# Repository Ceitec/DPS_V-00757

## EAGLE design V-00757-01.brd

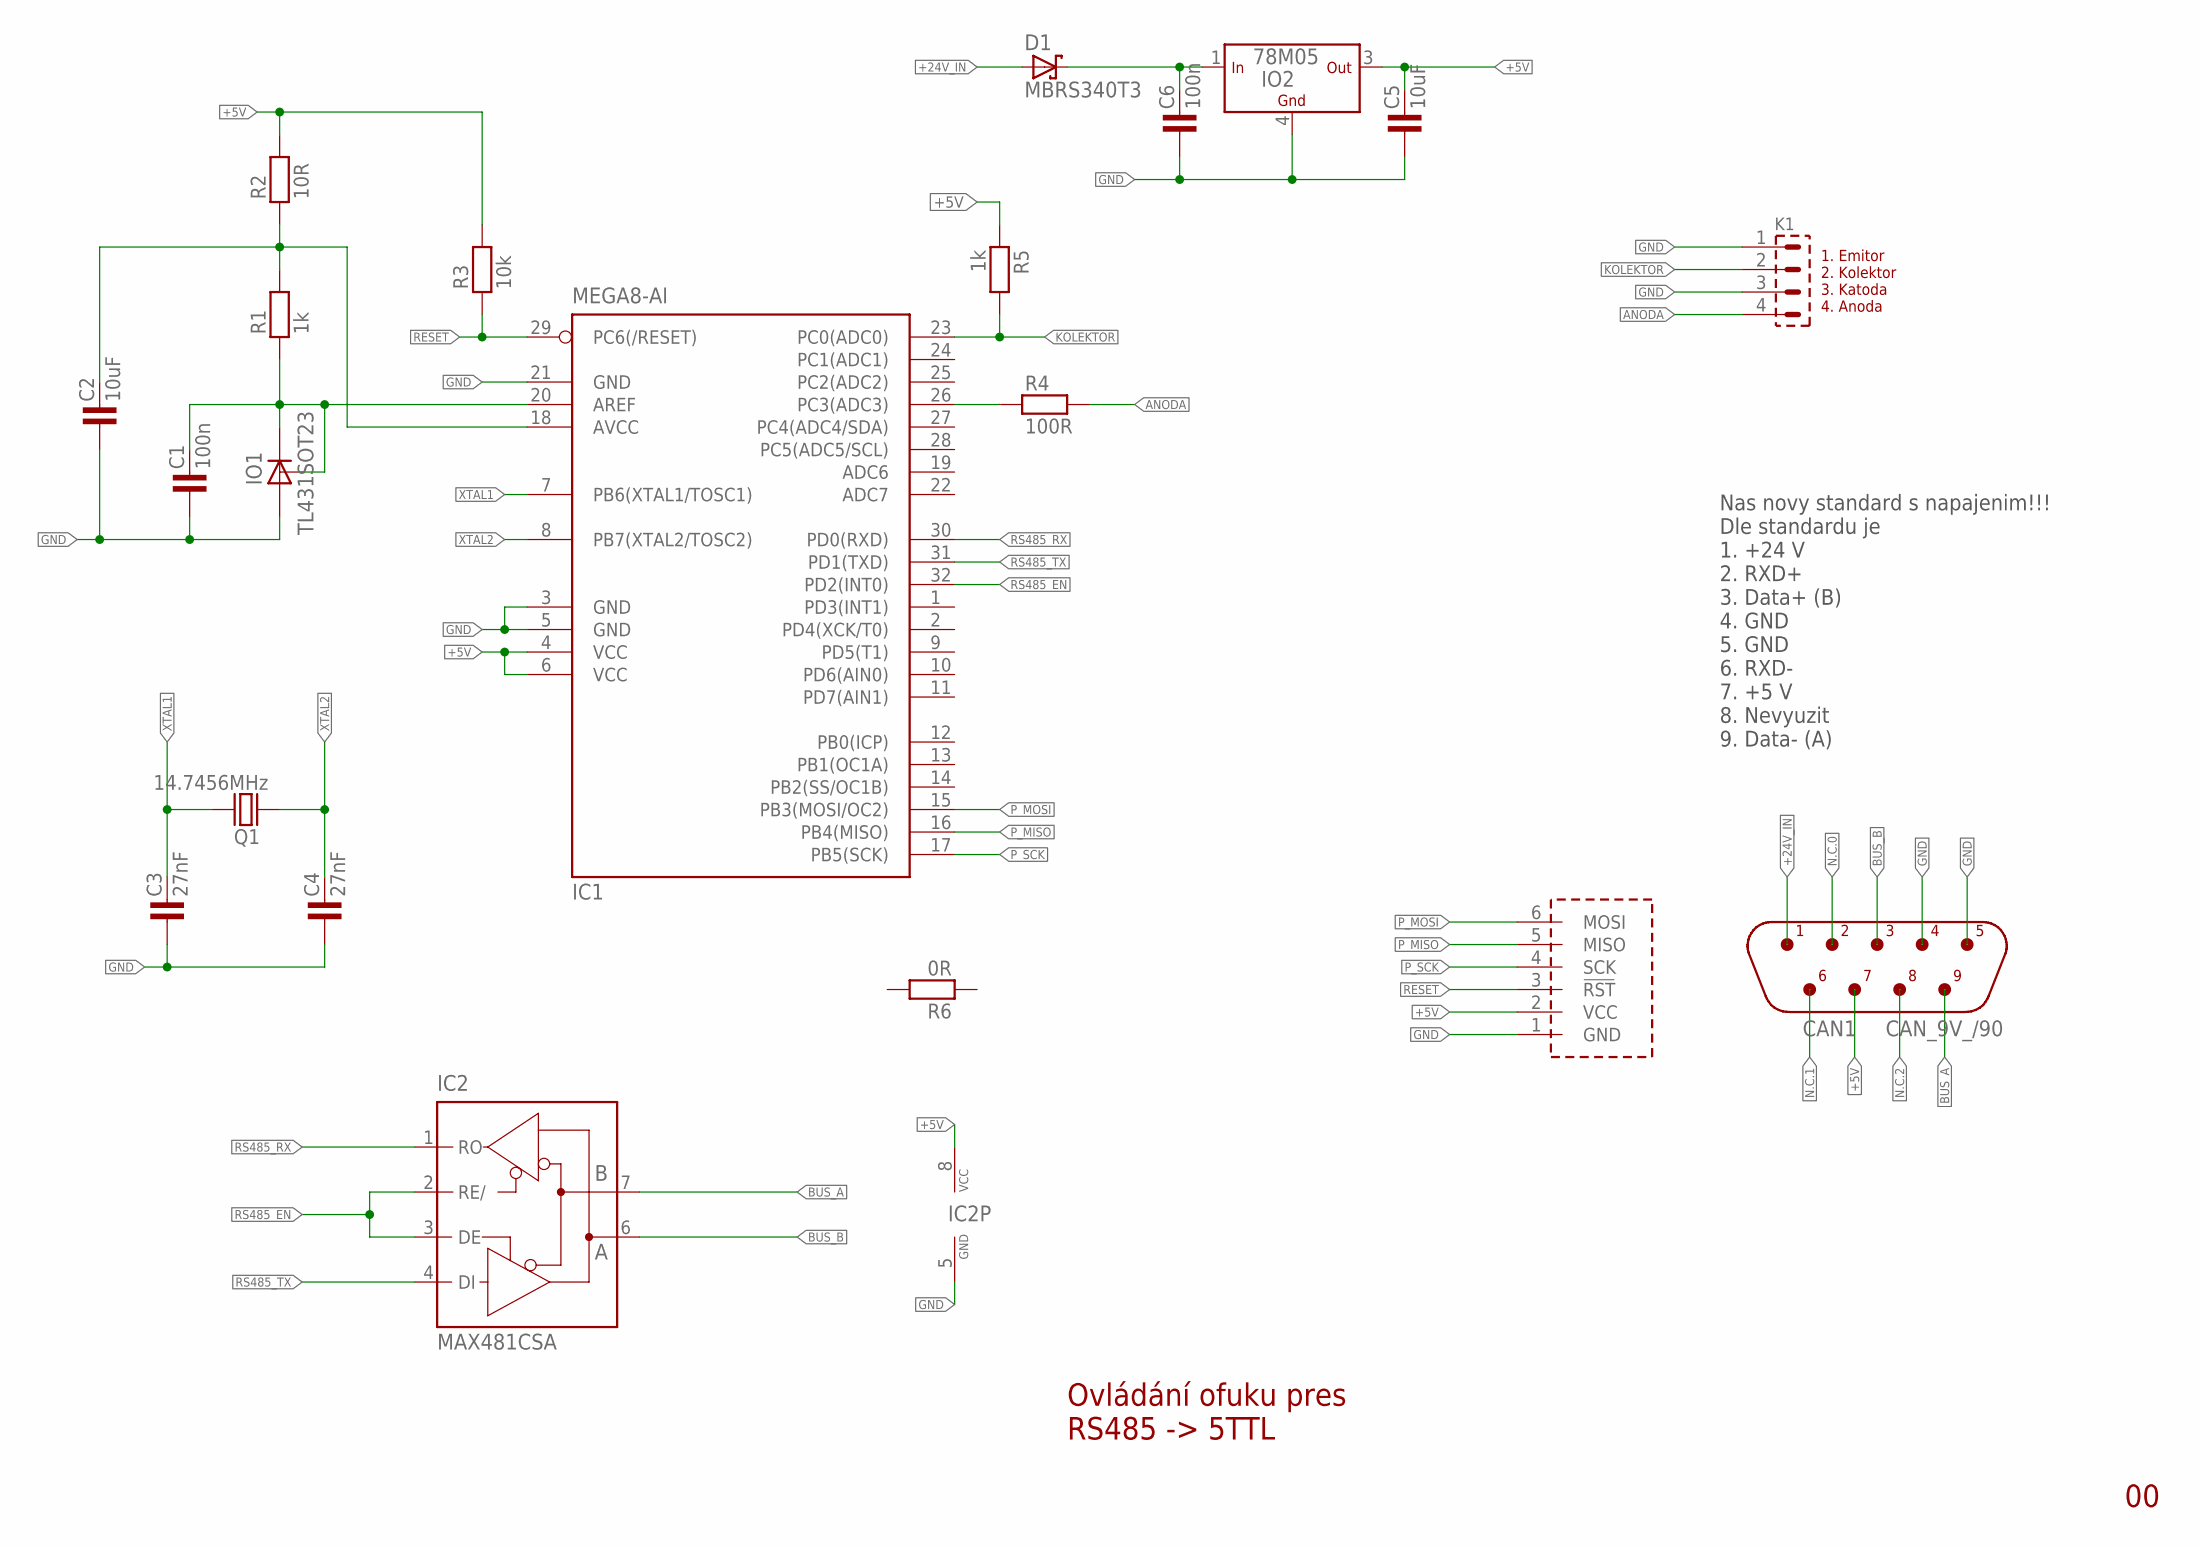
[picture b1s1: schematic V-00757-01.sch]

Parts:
C1, C6: 100n; 1206
C2, C5: 10uF; 1206
C3, C4: 27nF; 0805
CAN1: CAN_9V_/90; CAN9V/90
D1: MBRS340T3; SMC
IC1: MEGA8-AI; TQFP32-08
IC2: MAX481CSA; SO08
IO1: TL431SOT23; SOT23
IO2: 78M05; DPAK
K1: PSH02-04W
Q1: 14.7456MHz; HC-49U
R1, R5: 1k; 1206
R2: 10R; 1206
R3: 10k; 1206
R4: 100R; 1206
R6: 0R; 1206
U$1: AVR_PROG_SPI; PSH02-06P

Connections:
+5V: C5.2, CAN1.7, IC1.4 (VCC), IC1.6 (VCC), IC2.8 (VCC), IO2.3 (OUT), R2.2, R3.2, R5.1, U$1.2 (VCC)
+24V: C6.2, D1.C, IO2.1 (IN)
+24V_IN: CAN1.1, D1.A
ANODA: K1.4, R4.2
BUS_A: CAN1.9, IC2.7 (B)
BUS_B: CAN1.3, IC2.6 (A)
GND: C1.1, C2.1, C3.1, C4.1, C5.1, C6.1, CAN1.4, CAN1.5, IC1.3 (GND), IC1.5 (GND), IC1.21 (GND), IC2.5 (GND), IO1.3 (A), IO2.4 (GND), K1.1, K1.3, U$1.1 (GND)
KOLEKTOR: IC1.23 (PC0(ADC0)), K1.2, R5.2
unnamed: C1.2, IC1.20 (AREF), IO1.1 (C), IO1.2 (R), R1.1
unnamed: IC1.26 (PC3(ADC3)), R4.1
unnamed: C2.2, IC1.18 (AVCC), R1.2, R2.1
N.C.0: CAN1.2
N.C.1: CAN1.6
N.C.2: CAN1.8
P_MISO: IC1.16 (PB4(MISO)), U$1.5 (MISO)
P_MOSI: IC1.15 (PB3(MOSI/OC2)), U$1.6 (MOSI)
P_SCK: IC1.17 (PB5(SCK)), U$1.4 (SCK)
RESET: IC1.29 (PC6(/RESET)), R3.1, U$1.3 (!RST)
RS485_EN: IC1.32 (PD2(INT0)), IC2.2 (RE/), IC2.3 (DE)
RS485_RX: IC1.30 (PD0(RXD)), IC2.1 (RO)
RS485_TX: IC1.31 (PD1(TXD)), IC2.4 (DI)
XTAL1: C3.2, IC1.7 (PB6(XTAL1/TOSC1)), Q1.2
XTAL2: C4.2, IC1.8 (PB7(XTAL2/TOSC2)), Q1.1

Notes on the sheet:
Ovládání ofuku pres RS485 -> 5TTL
1. Emitor 2. Kolektor 3. Katoda 4. Anoda
Nas novy standard s napajenim!!! Dle standardu je 1. +24 V 2. RXD+ 3. Data+ (B) 4. GND 5. GND 6. RXD- 7. +5 V 8. Nevyuzit 9. Data- (A)

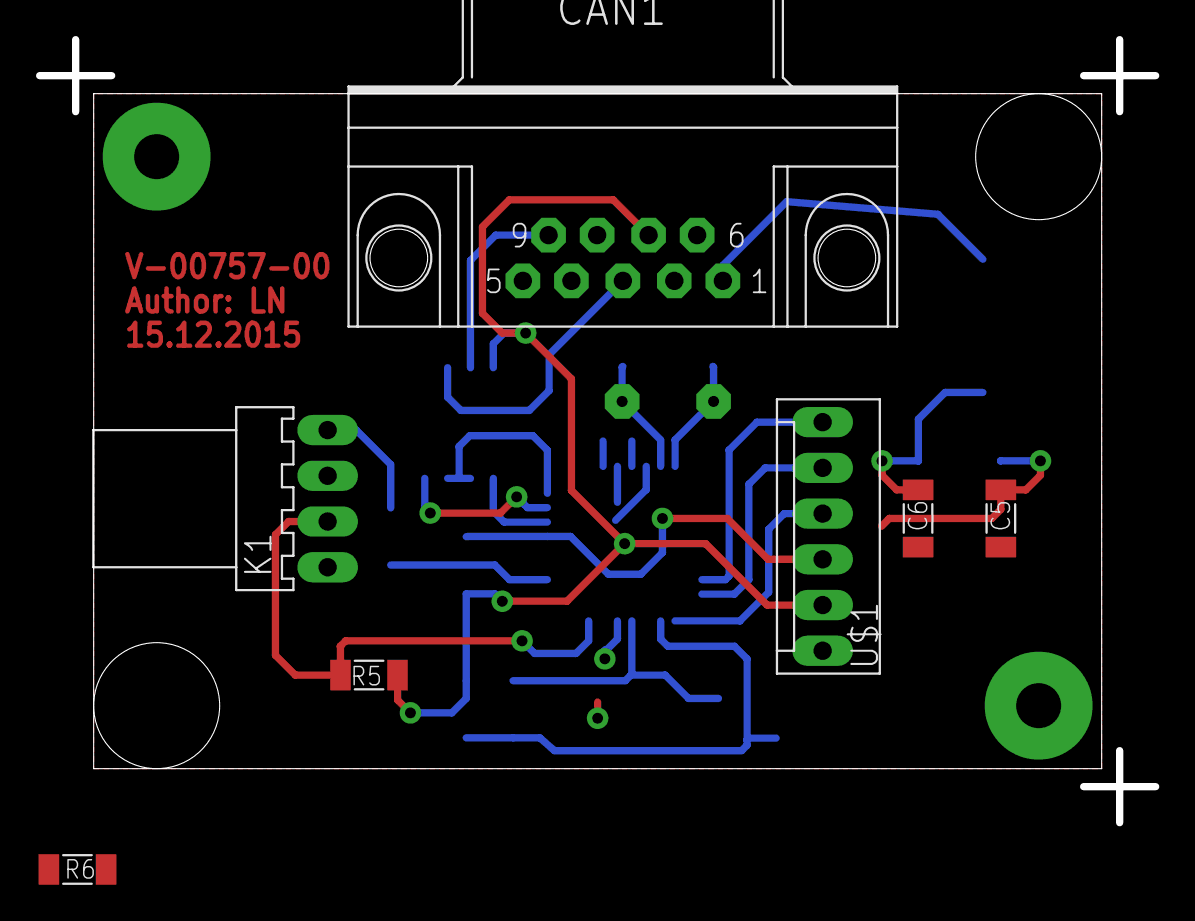
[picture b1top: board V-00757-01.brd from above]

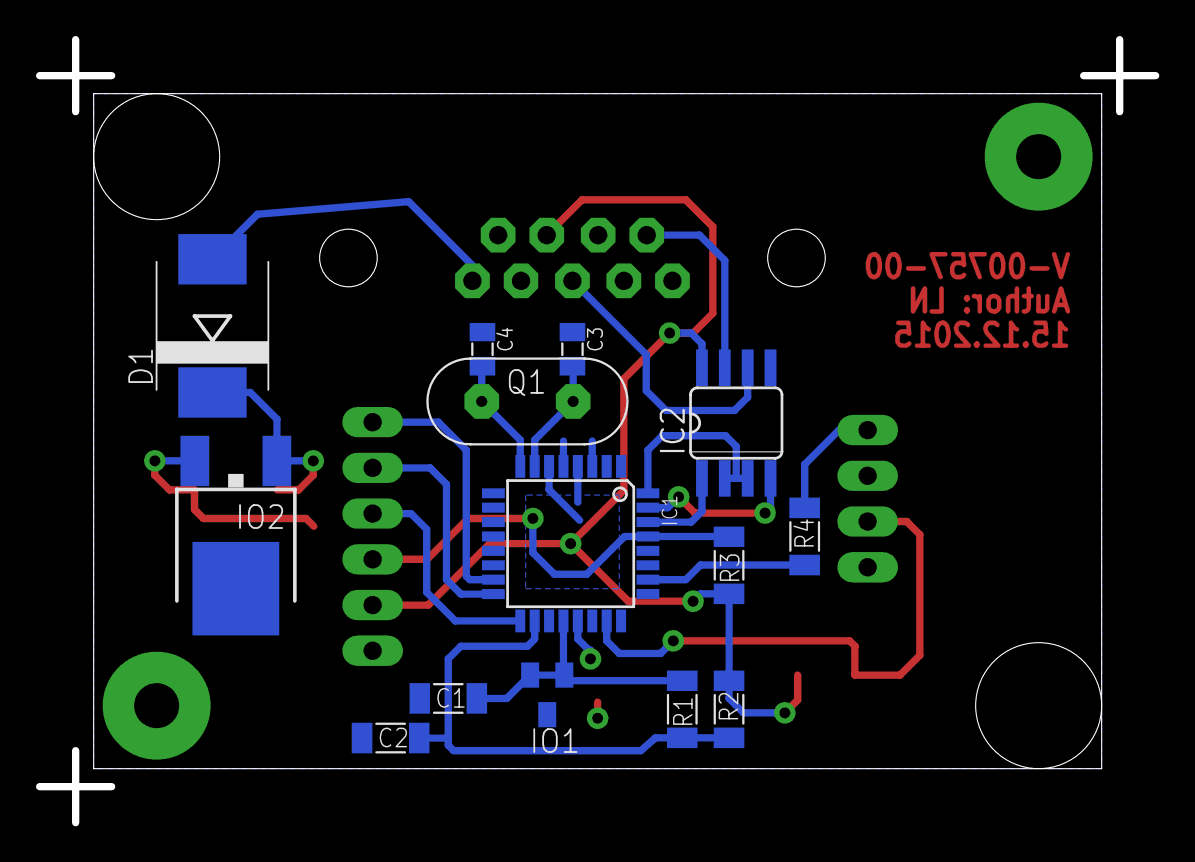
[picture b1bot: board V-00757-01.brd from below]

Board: 2 copper layers, 56.0 x 37.5 mm, 21 parts (14 on the bottom side), 20 nets.

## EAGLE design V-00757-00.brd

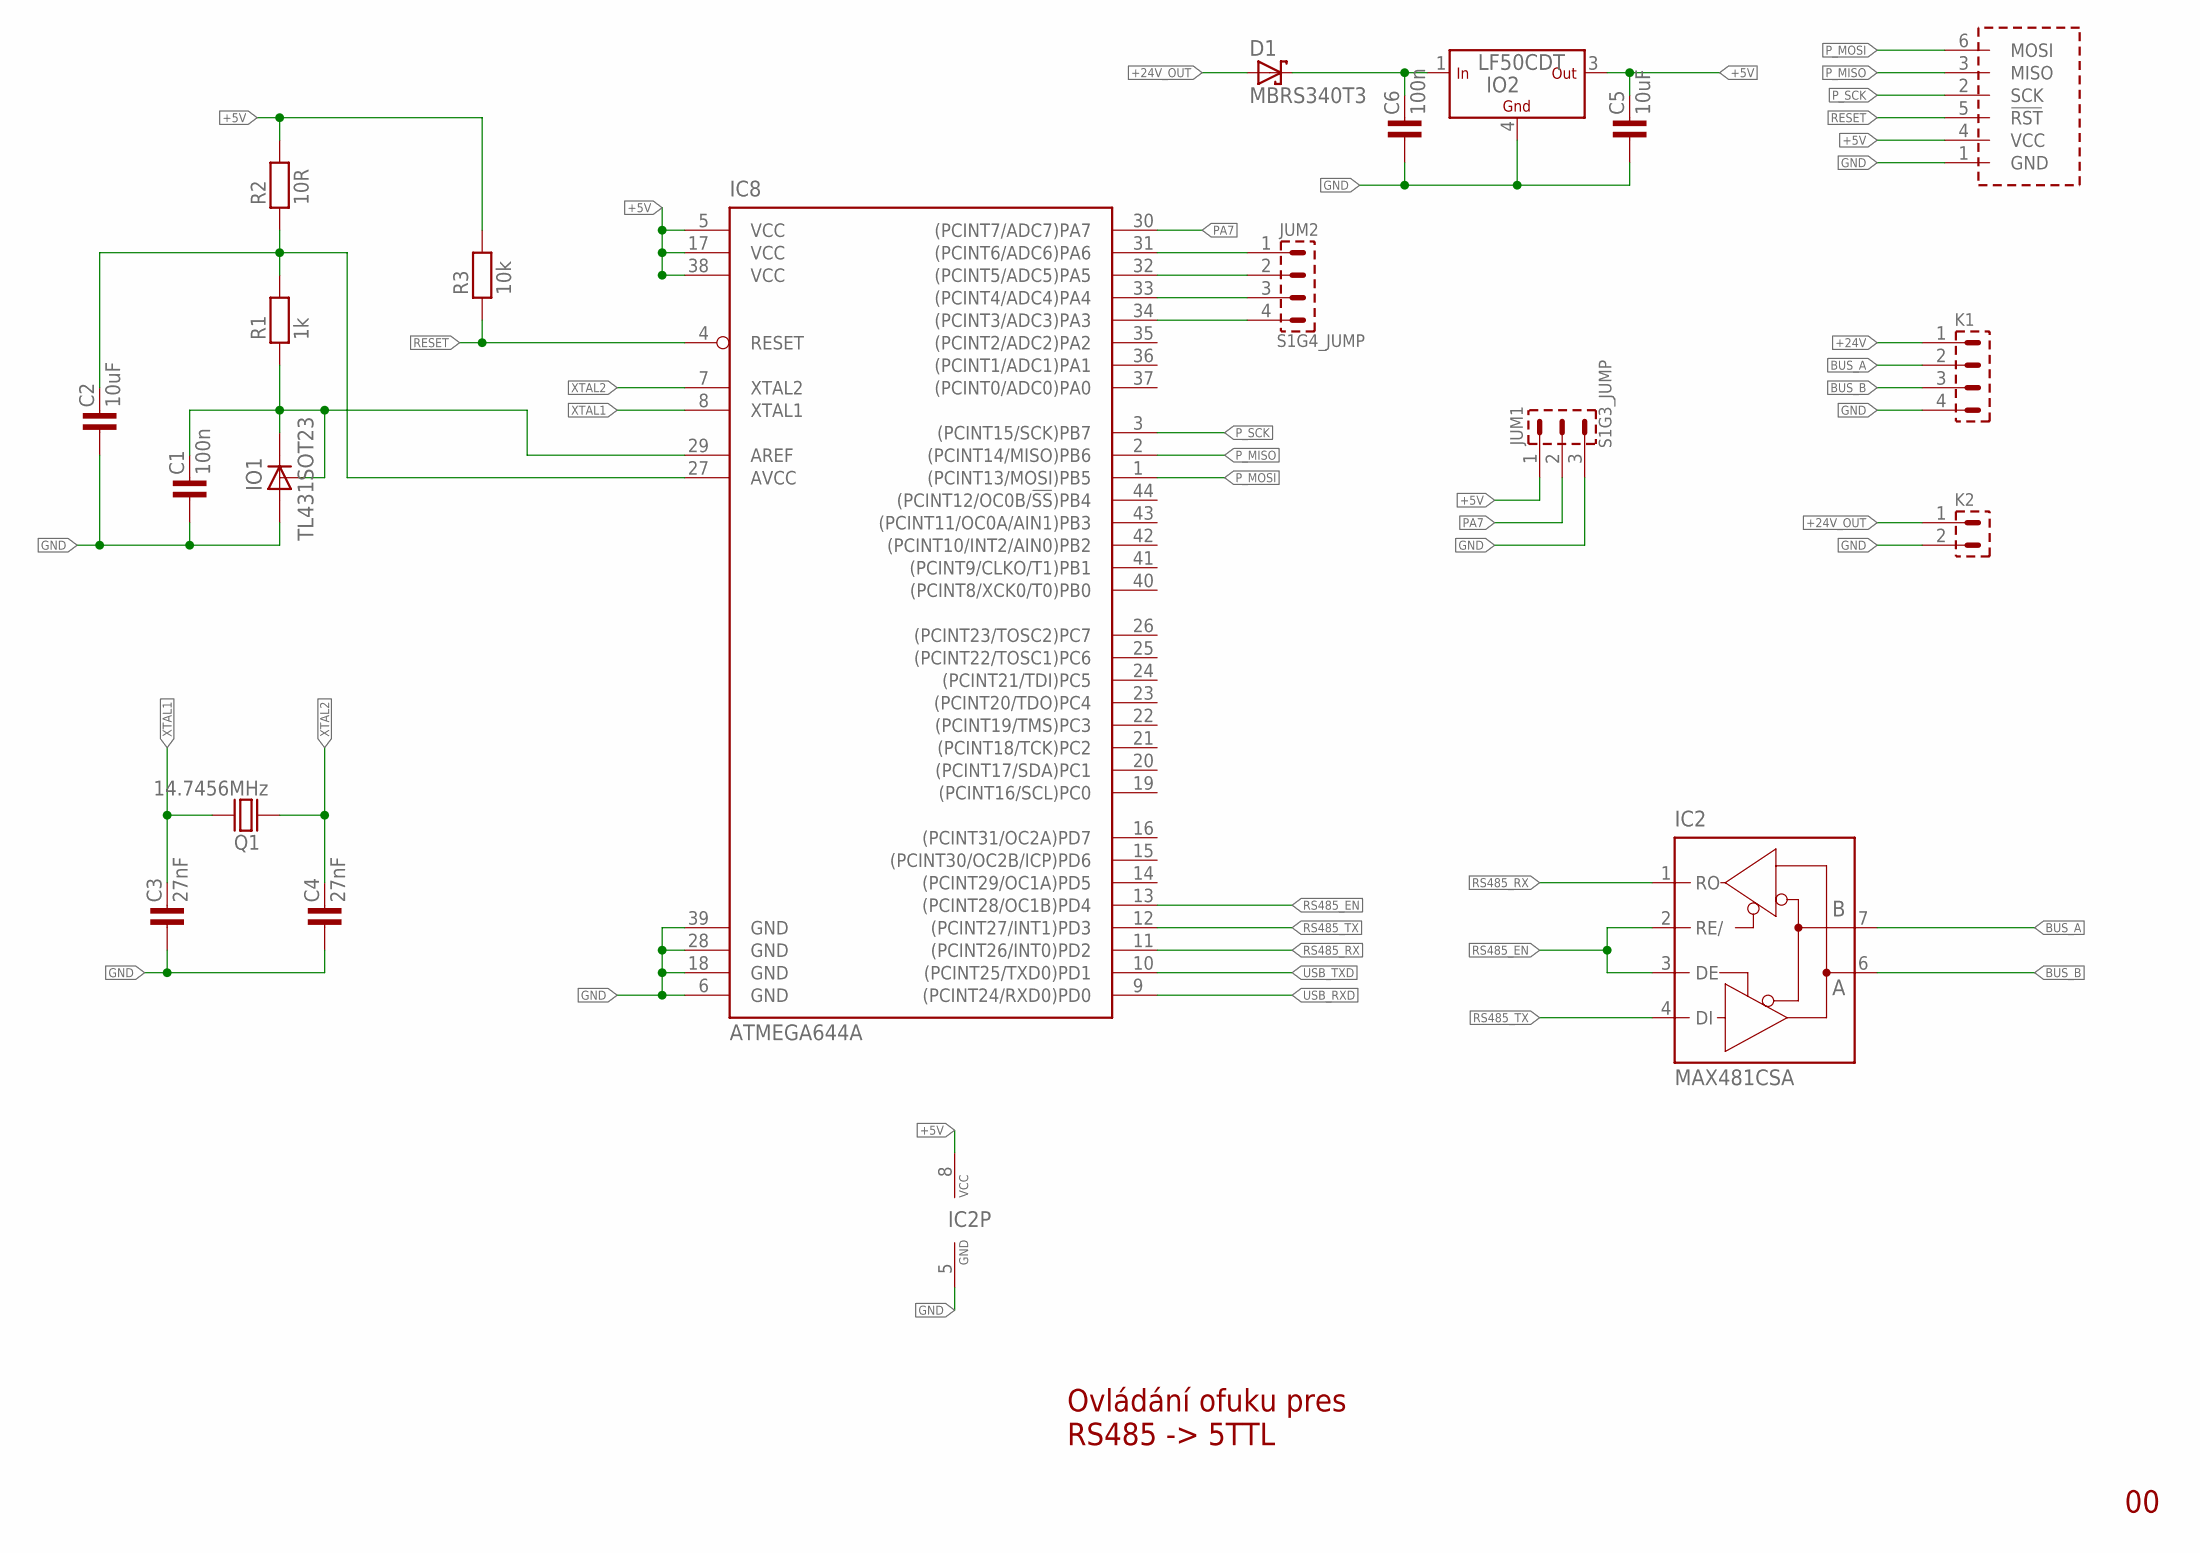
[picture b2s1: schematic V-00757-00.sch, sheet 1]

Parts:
C1, C6: 100n; 1206
C2, C5: 10uF; 1206
C3, C4: 27nF; 0805
D1: MBRS340T3; SMC
IC2: MAX481CSA; SO08
IC8: ATMEGA644A; TQFP44
IO1: TL431SOT23; SOT23
IO2: LF50CDT; DPAK
JUM1: S1G3_JUMP; S1G3_JUM
JUM2: S1G4_JUMP; S1G4_JUM
K1: PSH02-04P
K2: PSH02-02P
Q1: 14.7456MHz; HC-49U
R1: 1k; 1206
R2: 10R; 1206
R3: 10k; 1206
U$1: AVR_PROG_SPI; PSH02-06P

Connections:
+5V: C5.2, IC2.8 (VCC), IC8.5 (VCC), IC8.17 (VCC), IC8.38 (VCC), IO2.3 (OUT), JUM1.1, R2.2, R3.2, U$1.4 (VCC); also elsewhere on the board
+24V: C6.2, D1.C, IO2.1 (IN), K1.1
+24V_OUT: D1.A, K2.1
AREF: C1.2, IC8.29 (AREF), IO1.1 (C), IO1.2 (R), R1.1
AVCC: C2.2, IC8.27 (AVCC), R1.2, R2.1
BUS_A: IC2.7 (B), K1.2
BUS_B: IC2.6 (A), K1.3
GND: C1.1, C2.1, C3.1, C4.1, C5.1, C6.1, IC2.5 (GND), IC8.6 (GND), IC8.18 (GND), IC8.28 (GND), IC8.39 (GND), IO1.3 (A), IO2.4 (GND), JUM1.3, K1.4, K2.2, U$1.1 (GND); also elsewhere on the board
unnamed: IC8.31 ((PCINT6/ADC6)PA6), JUM2.1
unnamed: IC8.32 ((PCINT5/ADC5)PA5), JUM2.2
unnamed: IC8.33 ((PCINT4/ADC4)PA4), JUM2.3
unnamed: IC8.34 ((PCINT3/ADC3)PA3), JUM2.4
PA7: IC8.30 ((PCINT7/ADC7)PA7), JUM1.2
P_MISO: IC8.2 ((PCINT14/MISO)PB6), U$1.3 (MISO)
P_MOSI: IC8.1 ((PCINT13/MOSI)PB5), U$1.6 (MOSI)
P_SCK: IC8.3 ((PCINT15/SCK)PB7), U$1.2 (SCK)
RESET: IC8.4 (RESET), R3.1, U$1.5 (!RST)
RS485_EN: IC2.2 (RE/), IC2.3 (DE), IC8.13 ((PCINT28/OC1B)PD4)
RS485_RX: IC2.1 (RO), IC8.11 ((PCINT26/INT0)PD2)
RS485_TX: IC2.4 (DI), IC8.12 ((PCINT27/INT1)PD3)
USB_RXD: IC8.9 ((PCINT24/RXD0)PD0); also elsewhere on the board
USB_TXD: IC8.10 ((PCINT25/TXD0)PD1); also elsewhere on the board
XTAL1: C3.2, IC8.8 (XTAL1), Q1.2
XTAL2: C4.2, IC8.7 (XTAL2), Q1.1

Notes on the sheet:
Ovládání ofuku pres RS485 -> 5TTL

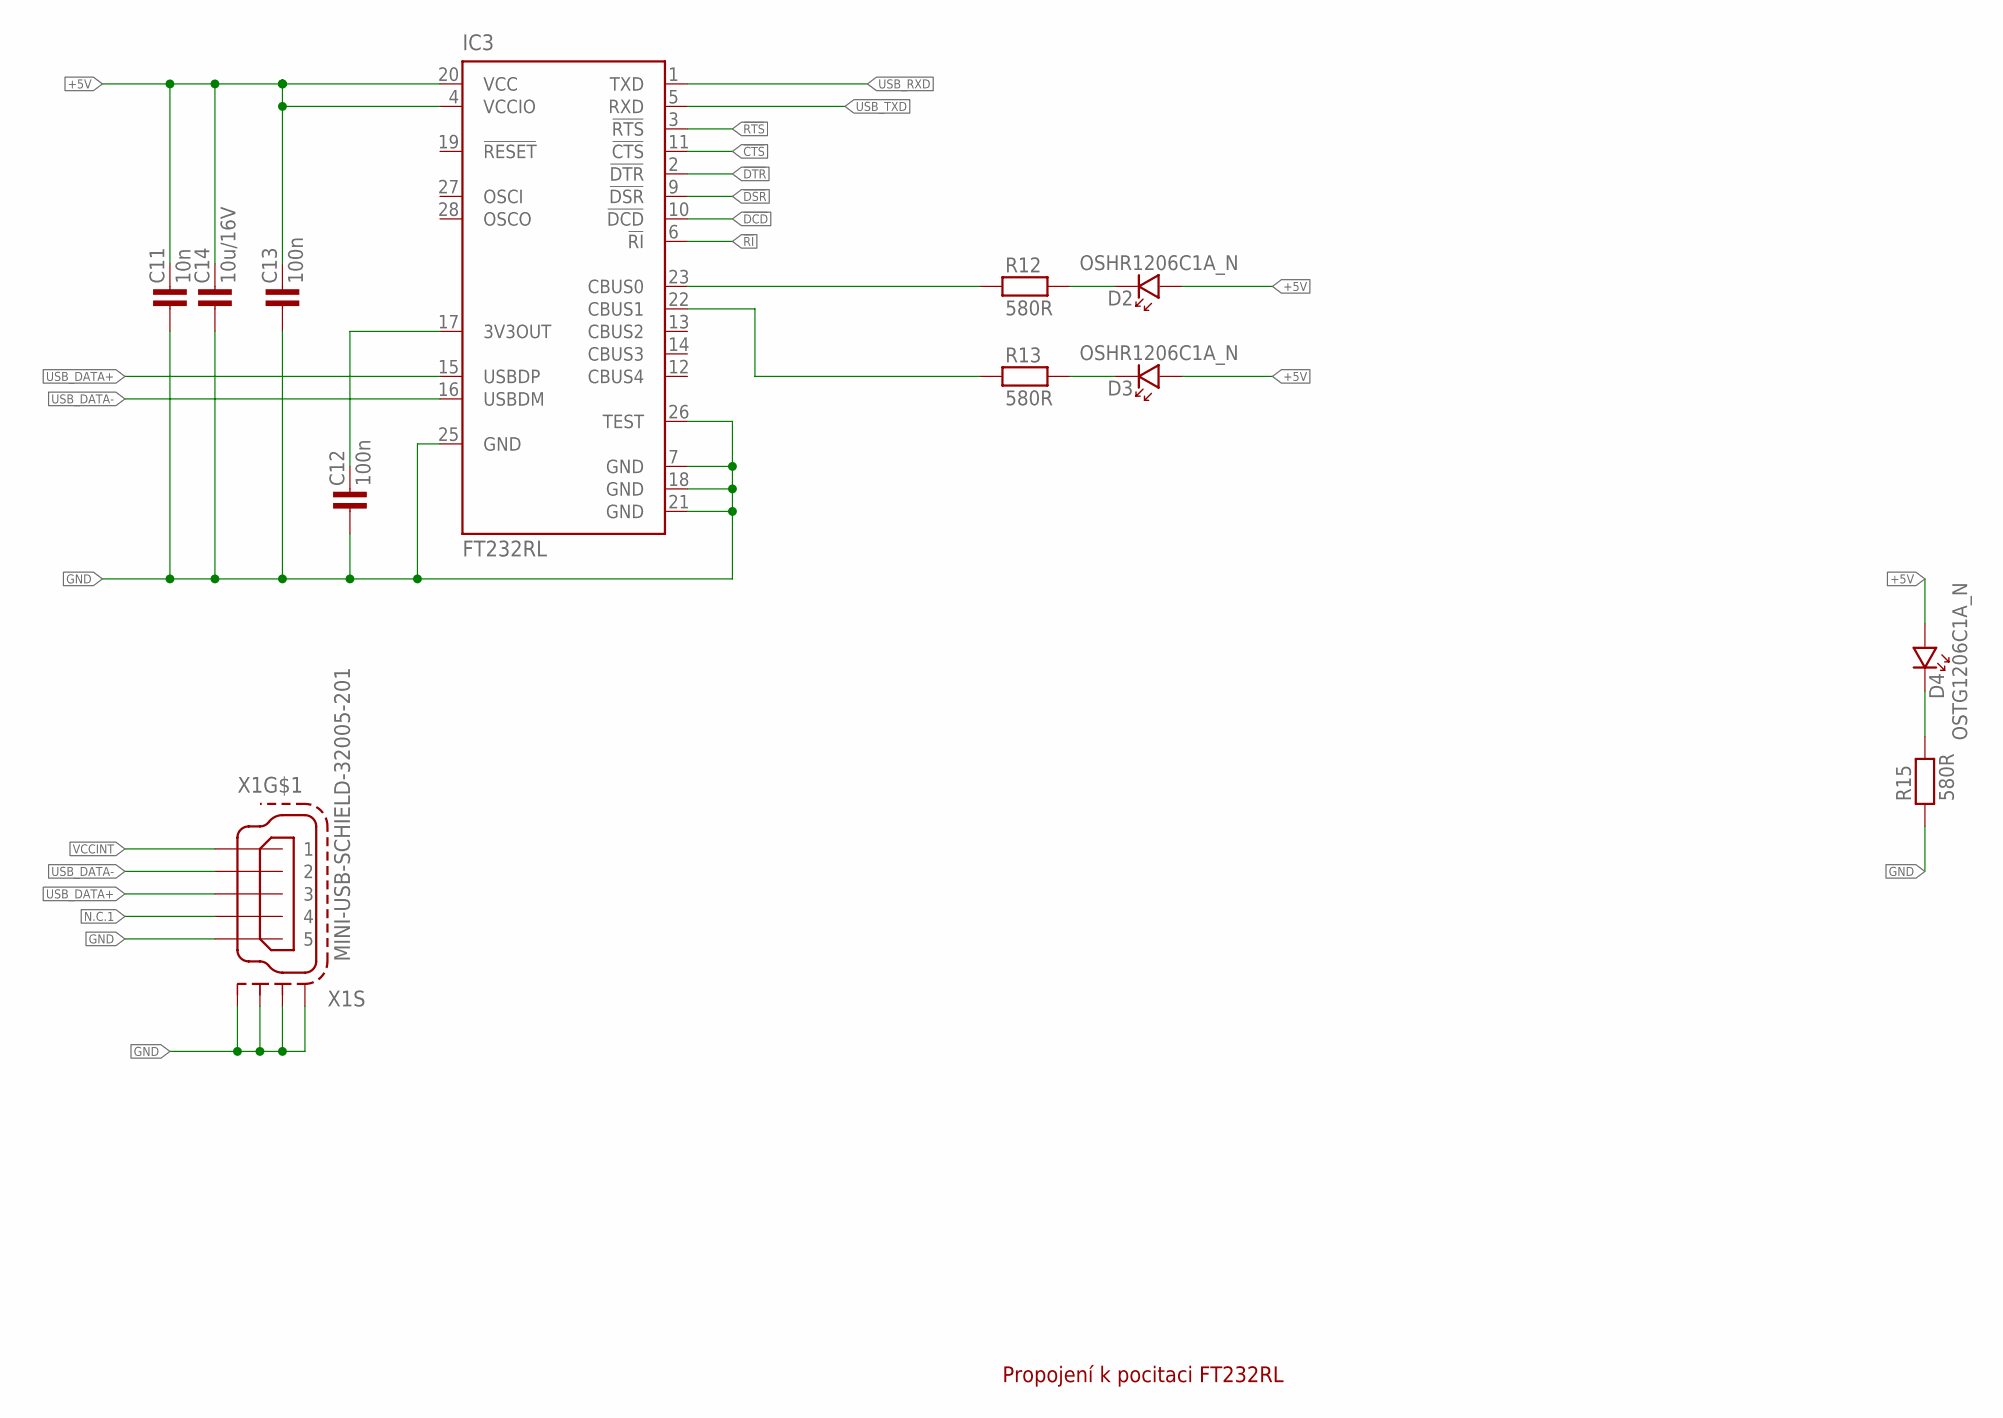
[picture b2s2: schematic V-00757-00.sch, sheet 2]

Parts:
C11: 10n; 1206
C12, C13: 100n; 1206
C14: 10u/16V; 1206
D2, D3: OSHR1206C1A_N; P1206
D4: OSTG1206C1A_N; P1206
IC3: FT232RL; SSOP28
R12, R13, R15: 580R; 1206
X1: MINI-USB-SCHIELD-32005-201; 32005-201

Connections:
!CTS: IC3.11 (!CTS)
!DCD: IC3.10 (!DCD)
!DSR: IC3.9 (!DSR)
!DTR: IC3.2 (!DTR)
!RI: IC3.6 (!RI)
!RTS: IC3.3 (!RTS)
+5V: C11.2, C13.2, C14.2, D2.A, D3.A, D4.A, IC3.4 (VCCIO), IC3.20 (VCC); also elsewhere on the board
GND: C11.1, C12.1, C13.1, C14.1, IC3.7 (GND), IC3.18 (GND), IC3.21 (GND), IC3.25 (GND), IC3.26 (TEST), R15.1, X1.5, X1.M1 (S1), X1.M2 (S2), X1.M3 (S3), X1.M4 (S4); also elsewhere on the board
unnamed: IC3.23 (CBUS0), R12.1
unnamed: IC3.22 (CBUS1), R13.1
unnamed: C12.2, IC3.17 (3V3OUT)
unnamed: D2.K, R12.2
unnamed: D3.K, R13.2
unnamed: D4.K, R15.2
N.C.1: X1.4
USB_DATA+: IC3.15 (USBDP), X1.3
USB_DATA-: IC3.16 (USBDM), X1.2
USB_RXD: IC3.1 (TXD); also elsewhere on the board
USB_TXD: IC3.5 (RXD); also elsewhere on the board
VCCINT: X1.1

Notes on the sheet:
Propojení k pocitaci FT232RL

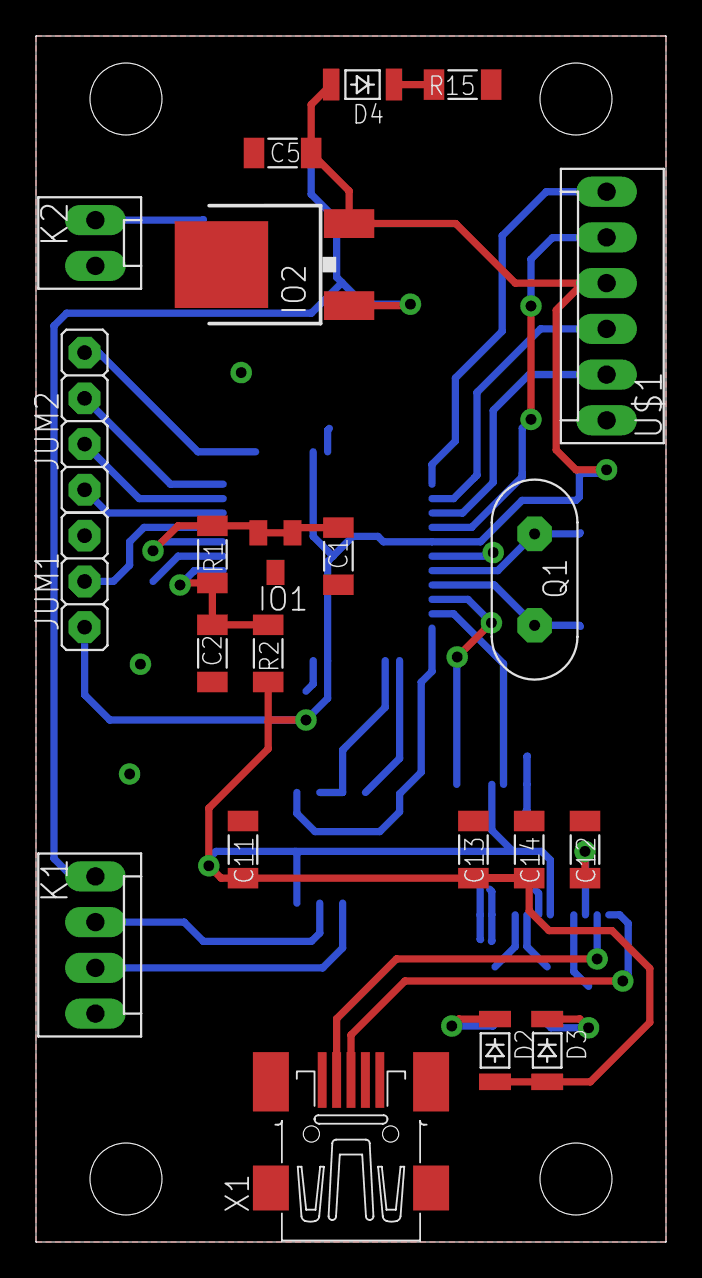
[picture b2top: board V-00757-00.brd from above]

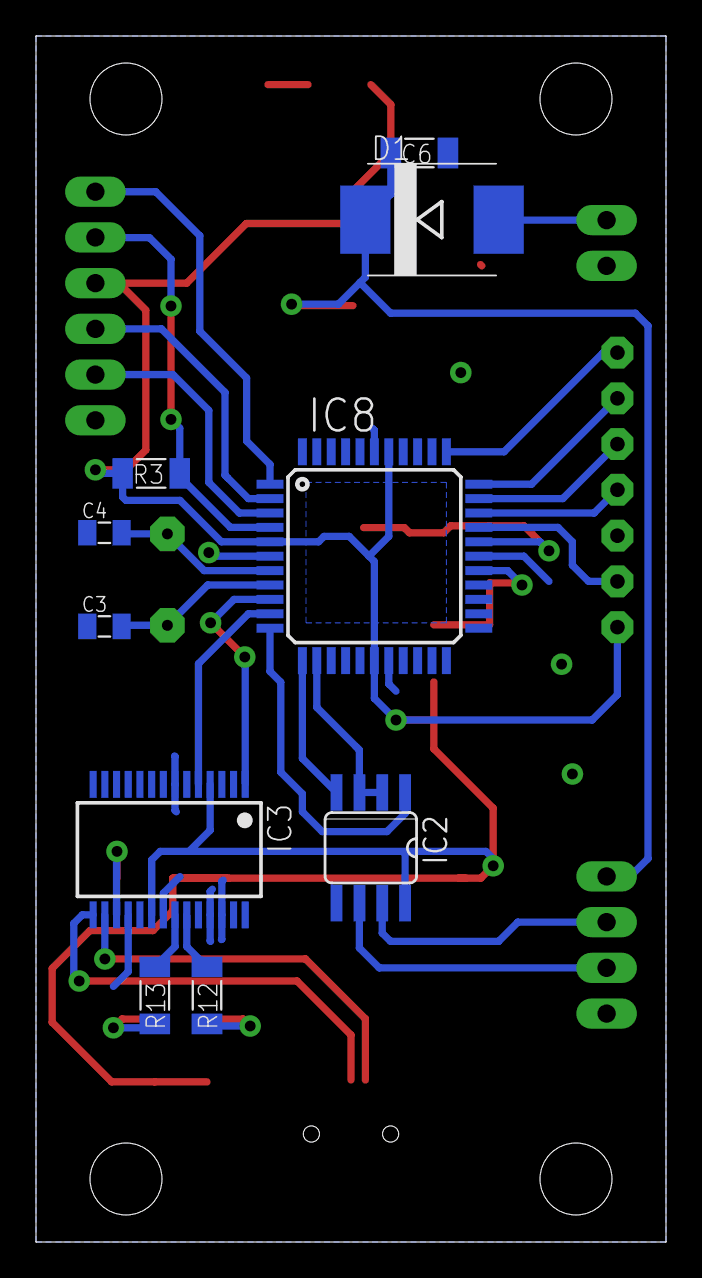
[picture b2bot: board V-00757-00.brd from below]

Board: 2 copper layers, 35.0 x 67.0 mm, 32 parts (10 on the bottom side), 32 nets.

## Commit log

2015-12-11 :tada: Added .gitattributes & .gitignore files
2015-12-11 v.1.1.0.0
2015-12-29 v1.1.0.2
2016-02-10 v.2.0

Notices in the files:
parts and their libraries:
Copyright (C) PaJa 2001-2014
Copyright (C) PaJa 2011-2014
